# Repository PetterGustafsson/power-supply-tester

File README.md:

<p align="center">
  
</p>

# Power supply tester

**Twelve inputs. One supply. A little theatre on the desk.**

Rev D2 measurement PCB · I15 enclosure · ESP32-S3 · 240 × 240 round LCD

The tester identifies positive and return contacts from one common DC supply.
Chrome reflections, brass pins and orange locating keys give the idle display
its character. Applying voltage starts a one-second optical seating animation,
followed by live voltage, polarity and animated current artwork. The red Allied
Vision emblem at six o'clock currently recognizes the **1–2 pair**.

The opening render cycles through **idle → recognized pair → other powered pair**,
including the one-second optical seating transition. Download the
[6000 × 4500 still](output/product-render/power-supply-tester-hero.png) or
[6000 × 4500 animated master](output/product-render/power-supply-tester-three-modes-6000.gif).

*The animation uses illustrative voltage. The device uses its ADC readings to
drive the live display.*

## The current build

The October 23 firmware is the version the operator confirmed working: the
1–2 cable responds in approximately **1–2 seconds and stays powered**. Source,
the exact installed application binary, its display asset and build hashes are
included. [Build and flash guide →](docs/BUILD.md)

| Part of the project | Start here |
| --- | --- |
| Enclosure, ready to print | [I15 as-built 3MF and four STLs](case-cad/current/) |
| Preserved original CAD and earlier revisions | [CAD guide](case-cad/README.md) |
| Working measurement firmware | [Tester12VRevD source](firmware/Tester12VRevD/) |
| Exact working firmware + optical asset | [October 23 binary package](firmware/releases/d2-live-2026-10-23/) |
| PCB schematic, layout, BOM, Gerbers and CPL | [Rev D2 hardware](hardware/rev-d/README.md) |
| Finished product rendering and animation | [6K still](output/product-render/power-supply-tester-hero.png) · [6K GIF](output/product-render/power-supply-tester-three-modes-6000.gif) · [scene and regeneration guide](output/product-render/README.md) |
| Assembly poster | [A2 PDF](output/pdf/power-supply-tester-final-layout.pdf) · [full-resolution PNG](output/final-layout-poster/power-supply-tester-final-layout.png) |
| Poster scene and parts list | [Blender scene](output/final-layout-poster/final-layout.blend) · [parts manifest](output/final-layout-poster/parts-manifest.json) |
| Artwork sources and generation | [Scripts](scripts/) · [art and build guide](docs/BUILD.md#artwork-and-poster) |
| Calibration and bench testing | [Local calibration UI](tools/calibration-ui/README.txt) · [firmware/calibration guide](firmware/Tester12VRevD/README.md) |
| Timing, installation and regression evidence | [October 23 record](output/fast-response-2026-10-23/flash-evidence.json) |

## The assembly

| Hardware | Quantity | Use |
| --- | ---: | --- |
| M2 × 6 mm, black flat Phillips self-tapping screws | 6 | Four for the PCB, two for the display |
| M2.5 × 10 mm, black flat Phillips self-tapping screws | 4 | Case |
| 2 mm foam pad | 1 | USB support |
| 4-inch soft flat USB-C extension, 90° male to female | 1 | Internal USB connection |
| Twelve-core HR10A connector cable with ferrule ends | 1 | Twelve sensing inputs |
| Five-wire display harness | 1 | Display-to-PCB connection |
| Rubber feet | 4 | Base |
| Cable tie | 1 | Cable strain relief |

The [as-built print plate](case-cad/current/PSU_case_I15_as_built.3mf) contains
the base, shell, crown and display retainer. The preserved original I15 package
also contains the earlier printed shim; the current assembly uses the foam pad.
The poster shows the display as unpowered black glass and the USB cable straight.

Selected components: [screw assortment](https://www.amazon.com/dp/B0G24Z3P66),
[USB extension](https://www.amazon.com/dp/B0D9XGFW3W).

## Display art

- **Idle:** numbered brass contacts and orange orientation sheen.
- **Seating:** optical travel across one second.
- **Recognized pair:** static red emblem, cold-to-gold discharge and a spectral helix.
- **Other pairs:** muted crossed emblem with live polarity effects.

The previews show the visual design. The firmware samples 21 travel frames
across the one-second transition; playback and render timing are recorded in
the device logs. The electrical overlays illustrate classified polarity.

## Electronics and validation

The non-touch Waveshare ESP32-S3-LCD-1.28 handles the display and measurement
firmware. Four ADS1115 devices on the isolated measurement PCB provide twelve
sensing channels and a reference channel. See the
[hardware guide](hardware/rev-d/README.md) for the supported connection model,
limits, pin numbering and harness wiring.

The current prototype uses the measured input-1 gain shared with inputs 2–12,
with copied calibration provenance retained. Complete individual-channel
calibration and independent accuracy qualification remain in the
[calibration guide](firmware/Tester12VRevD/README.md). Noisy batches can produce
a filtered provisional LCD estimate while the strict measurement CSV rejects
them. The display response improvement preserves that distinction.

## Build and test

```sh
python3 -m venv .venv
source .venv/bin/activate
python -m pip install -r requirements.txt

clang++ -std=c++17 -O2 hardware/rev-d/scripts/test_preview_detection.cpp -o /tmp/tester-preview
/tmp/tester-preview
python hardware/rev-d/scripts/test_integration.py
python hardware/rev-d/scripts/test_calibration_commands.py
```

These tests use simulated hardware and do not open the tester's USB port.
Firmware compilation, binary recovery, artwork generation and poster rendering
are documented in [BUILD.md](docs/BUILD.md).

## Project map

```text
case-cad/        Current printable enclosure and historical CAD/reference exports
firmware/        Measurement source, display demos and the working binary package
hardware/        KiCad sources, manufacturing exports, sourcing and validation
scripts/         Artwork, optical assets, enclosure export and poster generation
tools/           Local calibration and supply-test interface
assets/          Fonts and their license/source records
docs/            Build guide and README artwork
output/          Posters, display assets and engineering/test evidence
references/      Manufacturer drawings and reference material
```

Historical hardware packages and art studies are retained with their revision
names. The links in **The current build** identify this prototype's baseline.
Third-party fonts, code, logos and models retain their original terms; see
[third-party notices](THIRD_PARTY_NOTICES.md).

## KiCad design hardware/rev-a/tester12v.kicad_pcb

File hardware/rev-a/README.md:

# 12 V pin-voltage tester — Rev A prototype

This is an actual KiCad 9 schematic and routed PCB, designed for a nominal **12 V DC source on any two of twelve inputs**, in either polarity. The other inputs are normally open. It measures voltage; it does not supply 12 V, switch power between connector pins, perform a load test, or prove which wire is earth/chassis ground.

**Status: prototype fabrication package with completed computer checks. No assembled Rev A board has been bench tested.** Component substitutions, assembled-board accuracy, power sequencing, and the display harness still require the first-article checks below. Do not interpret the simulations as a guarantee of operation.

The copper, holes, placements, and board outline in this render come from `tester12v.kicad_pcb`. Standard library component bodies are representative; the RECOM converter uses a generic SOIC body with a similar outline. This is not the earlier generated concept image. The **Waveshare ESP32-S3-LCD-1.28 non-touch** round display/controller connects by a five-wire harness and mounts separately. Display mounting holes or an enclosure are not part of this PCB.

## Files to use

- `../tester12v-rev-a-jlc-order.zip`: concise order handoff. Extract it, then upload `PCB-Gerbers.zip`, `BOM.csv` and `CPL.csv` to their respective JLC steps. Read `ORDER-INSTRUCTIONS.txt` first; U7 sourcing remains unresolved. This bundle contains the primary optimized BOM only.
- `tester12v.kicad_pro`, `tester12v.kicad_sch`, `bank1..3.kicad_sch`, `tester12v.kicad_pcb`: editable native design.
- `previews/schematic.pdf`, `previews/assembly.pdf`: circuit and component-location drawings.
- `previews/tester12v.step`: board/component geometry for mechanical review, subject to the model limitation above.
- `manufacturing/tester12v-rev-a-fabrication.zip`: Gerber and drill package for bare PCBs.
- `manufacturing/bom-grouped.csv`, `manufacturing/placements-smd.csv`: component purchasing/assembly information. R43 and R44 are **DNP**. J1–J4 are through-hole parts, omitted from the SMD placement file.
- `manufacturing/jlc-bom.csv`, `manufacturing/jlc-cpl.csv`: JLC upload files with exact library codes and all 114 fitted components, including J1–J4. See the sourcing blocker below before releasing an order.
- `sourcing/JLC-BOM-review.xlsx`, `sourcing/jlc-review.json`: dated price, stock, substitution and fee comparison.
- `validation/REPORT.md`: methods, results, assumptions, and limits of the checks.
- `../../firmware/Tester12V/`: live measurement firmware. The older `ConnectorDisplay` sketch is still the simulated animation demo.

## JLC sourcing update — 2026-09-30

The BOM now uses 24 exact JLC part numbers: eight Basic and sixteen Extended. Twenty-three part types had sufficient displayed stock for the nominal two-board quantity. **U7, RECOM R05C05TE05S-R / C5338283, had zero stock and requires preorder; no lead time was displayed.** Obtain its confirmed delivery and price before releasing the assembly order. This update does not make the whole assembly immediately available.

Four ordinary resistor types and four capacitor types now use Basic parts. This avoids eight Economic PCBA loading fees, approximately **$24.56 per order** at JLC's published $3.07 rate. It is a fee saving, not a claim that the entire order is $24.56 cheaper: the stocked switch packaging costs more than its preorder-only alternative. Standard PCBA charges loading for Basic parts too, so the same saving does not apply there. [JLC assembly fee schedule](https://jlcpcb.com/help/article/pcb-assembly-price).

The 165 kΩ, 10 kΩ and 100 kΩ precision resistors remain the original Yageo 0.1%, 25 ppm/K parts. C1–C12/C28 change from an unavailable Murata part (preorder minimum 799) to stocked Yageo C62774, preserving 1 nF, 5%, 50 V and C0G/NP0. All other capacitor substitutions preserve nominal capacitance, tolerance and dielectric, with equal or higher voltage ratings. C24's Samsung C45783 is NRND but had over four million pieces in JLC stock; it is selected for this small prototype order, with a fresh lifecycle review required for ongoing production. MLCC effective capacitance and startup/shutdown behavior still require bench verification.

U4–U6 use stocked **ADG4612BRUZ-REEL7 / C207399**, the same TSSOP-16 chip with different shipping packaging. JLC displayed 41 pieces and $6.7450 each. The optional `manufacturing/jlc-bom-preorder-switches.csv` selects the original **ADG4612BRUZ / C657391** instead: zero stock, estimated nine-day lead time, MOQ four and estimated $2.7916 each. Six fitted switches could cost about $23.72 less, before attrition; consider this only if its confirmed lead time fits the converter wait. Use one BOM, not both.

At displayed 1+ unit prices, the primary BOM's nominal fitted parts for two boards total **$93.16**, including a **$20.97 unconfirmed converter preorder estimate**. The Economic loading allowance is another $49.12. These are not a checkout quote: PCB fabrication, setup, placement, attrition/spares, minimum-order overhead, shipping, tax, LCD module and harness are excluded. Nothing is reserved or ordered.

The JLC CPL uses the same origin as the Gerbers: X right, Y upward, millimetres; negative Y is intentional. J1–J4 use the centre of the footprint's F.Fab body rather than the pin-1 origin. SMD positions and rotations are unchanged. Inspect JLC's placement preview against `previews/assembly.pdf`, especially polarized parts and connector orientation; JLC library rotation conventions have not been validated in an order. Resolve converter sourcing, part matching and manufacturer DFM before payment. The populated count is 114; R43/R44 and test pads are excluded.

Sourcing changed only MPN/manufacturer/library metadata. The native PCB now also contains the optimized purchasing fields. All circuit values, pin nets, footprint geometry and routing are unchanged. Gerbers, drills, DNP-filtered stencil, placements, schematic and assembly PDFs have been regenerated. Exact drawing commands match the prior release after excluding export timestamps. ERC/DRC and the 356-pad connectivity audit pass; DC/transient and host firmware tests passed for the same unchanged circuit. No assembled-board tests have been performed.

## Board and electrical specification

| Item | Rev A |
|---|---|
| Board | 90 × 80 mm; two copper layers; 1.6 mm FR-4; 1 oz copper |
| Minimum routed trace / clearance | 0.20 mm / 0.20 mm netclass clearance |
| Through vias | 0.60 mm diameter / 0.30 mm finished drill |
| Mounting | Four 2.7 mm non-plated holes; centers (3,3), (87,3), (3,77), (87,77) mm |
| Inputs | Twelve high-impedance sense terminals; three four-position 3.5 mm screw terminals |
| Normal input range | 0–18 V DC between the active pair; optimized for 12 V |
| Fault target | 48 V DC differential miswire survival target, **not a qualified rating or accurate measurement range** |
| Power | Separate USB-domain 5 V and 3.3 V through J4 |
| Isolation | Isolated DC/DC plus I²C isolator; no copper crosses the 2.7 mm isolation corridor |
| ADCs | Three ADS1115, addresses 0x48, 0x49, 0x4A; ±4.096 V ADC scale; 3.3 V supply |
| Display | Existing Waveshare ESP32-S3-LCD-1.28, 240 × 240 GC9A01 |
| Accuracy | ±0.15 V around 12 V after calibration is a **bench acceptance target**, not a measured specification |
| Environment | Initial qualification at room temperature, clean/dry PCB, low-energy DC supplies |

The isolated ground floats with the connected supply. A displayed negative terminal is the lower-voltage terminal of the detected pair, not an earth-ground identification. Multiple rails and multiple connected returns can be ambiguous; the firmware rejects patterns that do not fit one live pair. This board is not a mains, CAT-rated, or automotive transient instrument. It is not a continuity tester for unpowered wires.

## Circuit operation

Each input passes through two 165 kΩ resistors. A 12 V Zener limits the source-side voltage of an ADG4612 switch; a 100 kΩ source bleed defines its voltage during startup. The switch connects to a 10 kΩ bias resistor, a 1 nF filter, and one ADC input. All three precision resistor values use 0.1% parts. The 100 kΩ bleed prevents the protection switch from staying in overvoltage isolation when a 12 V source is attached before USB power.

An OPA320 buffers half the isolated 3.3 V rail. R39 is a 220 Ω bleed that also discharges the bias node when power is removed. The TLV809EA30 supervisor enables the switches after the analog supply is established and disables them as the rail falls. D13 provides the TLV75533 regulator's output-to-input reverse-current path. Do not substitute the earlier MCP6001/1 kΩ/100 nF trial values.

The nominal differential scale, neglecting switch resistance and ADC loading, is:

`Vpair = (1 + 330k/10k + 330k/100k) × (VADC+ − VADC−) = 37.3 × ΔVADC`

An open ADC channel is approximately 1.50 V. At 12 V, the selected pair is approximately 1.34 V and 1.66 V. Firmware uses all twelve measurements to find the pair and its polarity. ADC loading, component tolerance, leakage, and different ADC gain errors require calibration for accurate readings. Scans are sequential, not a simultaneous oscilloscope capture.

## Display harness and power

Use the PCB connector's **pin numbers**, confirmed against the assembly drawing; do not infer wire order from a photograph. J4 is a JST XH five-position header. The mating housing is XHP-5 with appropriate XH contacts and insulated wire.

| J4 pin | PCB net | Existing Waveshare header connection |
|---|---|---|
| 1 | USB5V | Regulated USB-domain 5 V; H2 pin 3 VSYS is conditional as described below |
| 2 | USB_GND | H2 pin 1 GND |
| 3 | HOST3V3 | H2 pin 4, 3V3 |
| 4 | SDA_HOST | H2 pin 5, GPIO6 |
| 5 | SCL_HOST | H2 pin 7, GPIO7 |

The Waveshare schematic puts a Schottky diode between USB VBUS and VSYS. **Verify at least 4.5 V at U7's input after F1 while running**, and no more than 5.5 V. VSYS from a weak cable or low USB supply may not meet that minimum. If needed, feed J4 pin 1 from a regulated 5 V USB breakout/supply, sharing only the USB-domain ground. Do not connect an external 5 V source to the display's VSYS while also driving it from USB without reviewing that supply arrangement. Battery-only display operation does not provide the required tester supply.

R43/R44 stay unpopulated because the Waveshare module already has 4.7 kΩ I²C pull-ups on GPIO6/7. The isolated side has its own pull-ups. Use a short harness, initially no more than about 15 cm, and 100 kHz I²C. Never connect a DUT wire to J4 or bridge AGND to USB_GND during normal operation.

## First-article bench procedure

1. Inspect IC orientation, all diode cathodes, resistor values, solder bridges, and the 12 input paths against the assembly PDF. Confirm R43/R44 are absent. Clean flux before measuring leakage or calibrating.
2. With no DUT connected, check for supply shorts and for an unintended DC connection between USB_GND and AGND. Use an ordinary continuity/resistance test; do not apply a high-voltage insulation tester to the assembled board.
3. Power through J4 from a current-limited 5 V supply, initially limiting the tester's 5 V feed to 100 mA. Supply HOST3V3 from the display/controller. Check U7 input ≥4.5 V, isolated output near 5 V, A3V3 near 3.3 V, VBIAS near 1.65 V, and EN near 3.3 V after the supervisor delay. Investigate a sustained tester 5 V current above 100 mA. Measure actual consumption; the current budget is not a bench result.
4. Load the `Tester12V` sketch using the existing project flashing method. Its serial console runs at 115200 baud. Check all three ADC addresses and all twelve ADC readings near 1.50 V. Confirm unplugging the measurement board produces `ADC FAULT`, not a retained voltage.
5. Use an **isolated, current-limited** 12 V source, initially limited to 10 mA, between terminals 1 and 2. Check both polarities. The device draws only tens of microamps from this source; it does not load-test it.
6. Run all 132 ordered positive/negative pin pairs using `validation/bench-pairs.csv`. Record displayed pair, polarity, voltage, and the reference DMM reading. Calibrate before evaluating the ±0.15 V target. Also test no source, shorted pair, and an intentionally ambiguous multi-wire connection.
7. Check 3.3, 5, 9, 12, 15, and 18 V with representative pairs within one ADC and across different ADCs. Check settled accuracy, rise/fall response, and noise over at least 60 seconds.
8. Repeat power cycles with the 12 V DUT attached first, USB attached first, and removal/reconnection of each. Observe A3V3, VBIAS, EN, and representative ADC nodes with an isolated/differential probe. A grounded oscilloscope lead must not inadvertently bridge the isolation boundary. Check ADC nodes stay between AGND −0.3 V and A3V3 +0.3 V, and verify no persistent back-powering.
9. Only after the normal tests pass, evaluate the 24/48 V DC miswire target with a current-limited source, monitoring internal nodes and supply current. Do not claim a 48 V rating from the computer model alone. ESD, EMC, thermal extremes, and fast transients require separate qualification.

Record measured results and any board changes before ordering a larger batch.

## Calibration

Calibrate every channel with two known input voltages referred to **AGND on the isolated side**, using a floating precision source and DMM. This is a bench calibration arrangement, not the normal floating-pair connection. Do not connect the calibrator's return to USB_GND.

For each input, record the raw ADC voltage from serial CSV at a measured 0 V and a measured approximately +12 V on that terminal. Keep all other input terminals open. Average at least 32 settled readings per point. Calculate:

`gain = (Vhigh − Vlow) / (ADChigh − ADClow)`

`offset = Vlow − gain × ADClow`

Send `cal <pin 1..12> <gain> <offset>` over the serial console. Values persist in the ESP32's nonvolatile storage. For example, a measured gain near 37.3 is expected; the offset is often a large negative value because of the internal bias. **Use measured values, not this nominal example.** Complete all twelve channels; the firmware shows `FINISH CAL` while calibration is partial. `defaults` clears calibration and restores the nominal uncalibrated scale. Then disconnect the AGND calibration return and repeat floating-pair tests, including reversed polarity and cross-ADC pairs.

## Design sources

Pin assignments, ratings, and footprints were checked against the manufacturers' documents: [ADS1115](https://www.ti.com/lit/ds/symlink/ads1115.pdf), [ADG4612](https://www.analog.com/media/en/technical-documentation/data-sheets/adg4612_4613.pdf), [ISO1640B](https://www.ti.com/lit/ds/symlink/iso1640.pdf), [RECOM converter](https://recom-power.com/pdf/Econoline/RxxC05TExxS.pdf), [TLV755P](https://www.ti.com/lit/ds/symlink/tlv755p.pdf), [TLV809E family](https://www.ti.com/lit/ds/symlink/tlv803e.pdf), [OPA320](https://www.ti.com/lit/ds/symlink/opa320.pdf), [BZT52H](https://assets.nexperia.com/documents/data-sheet/BZT52H_SER.pdf), [PMEG2010ER](https://assets.nexperia.com/documents/data-sheet/PMEG2010ER.pdf), [Phoenix 1984633 terminal](https://www.phoenixcontact.com/en-us/products/printed-circuit-board-terminal-pt-15-4-35-h-1984633), and [Waveshare documentation](https://docs.waveshare.com/ESP32-S3-LCD-1.28).

Available PDF snapshots and source URLs are in `sources/`. Some manufacturer downloads were blocked; their documents were reviewed through the browser instead. Parts have not been reserved and stock, price, fabrication lead time, and assembler substitutions have not been confirmed.

The native PCB is the authoritative finished copper layout. `scripts/build_kicad.py` recreates **unrouted placement** and overwrites the PCB; run it only in a separate working copy. The routing scripts record the construction steps and are not a one-command regeneration of the finished release.

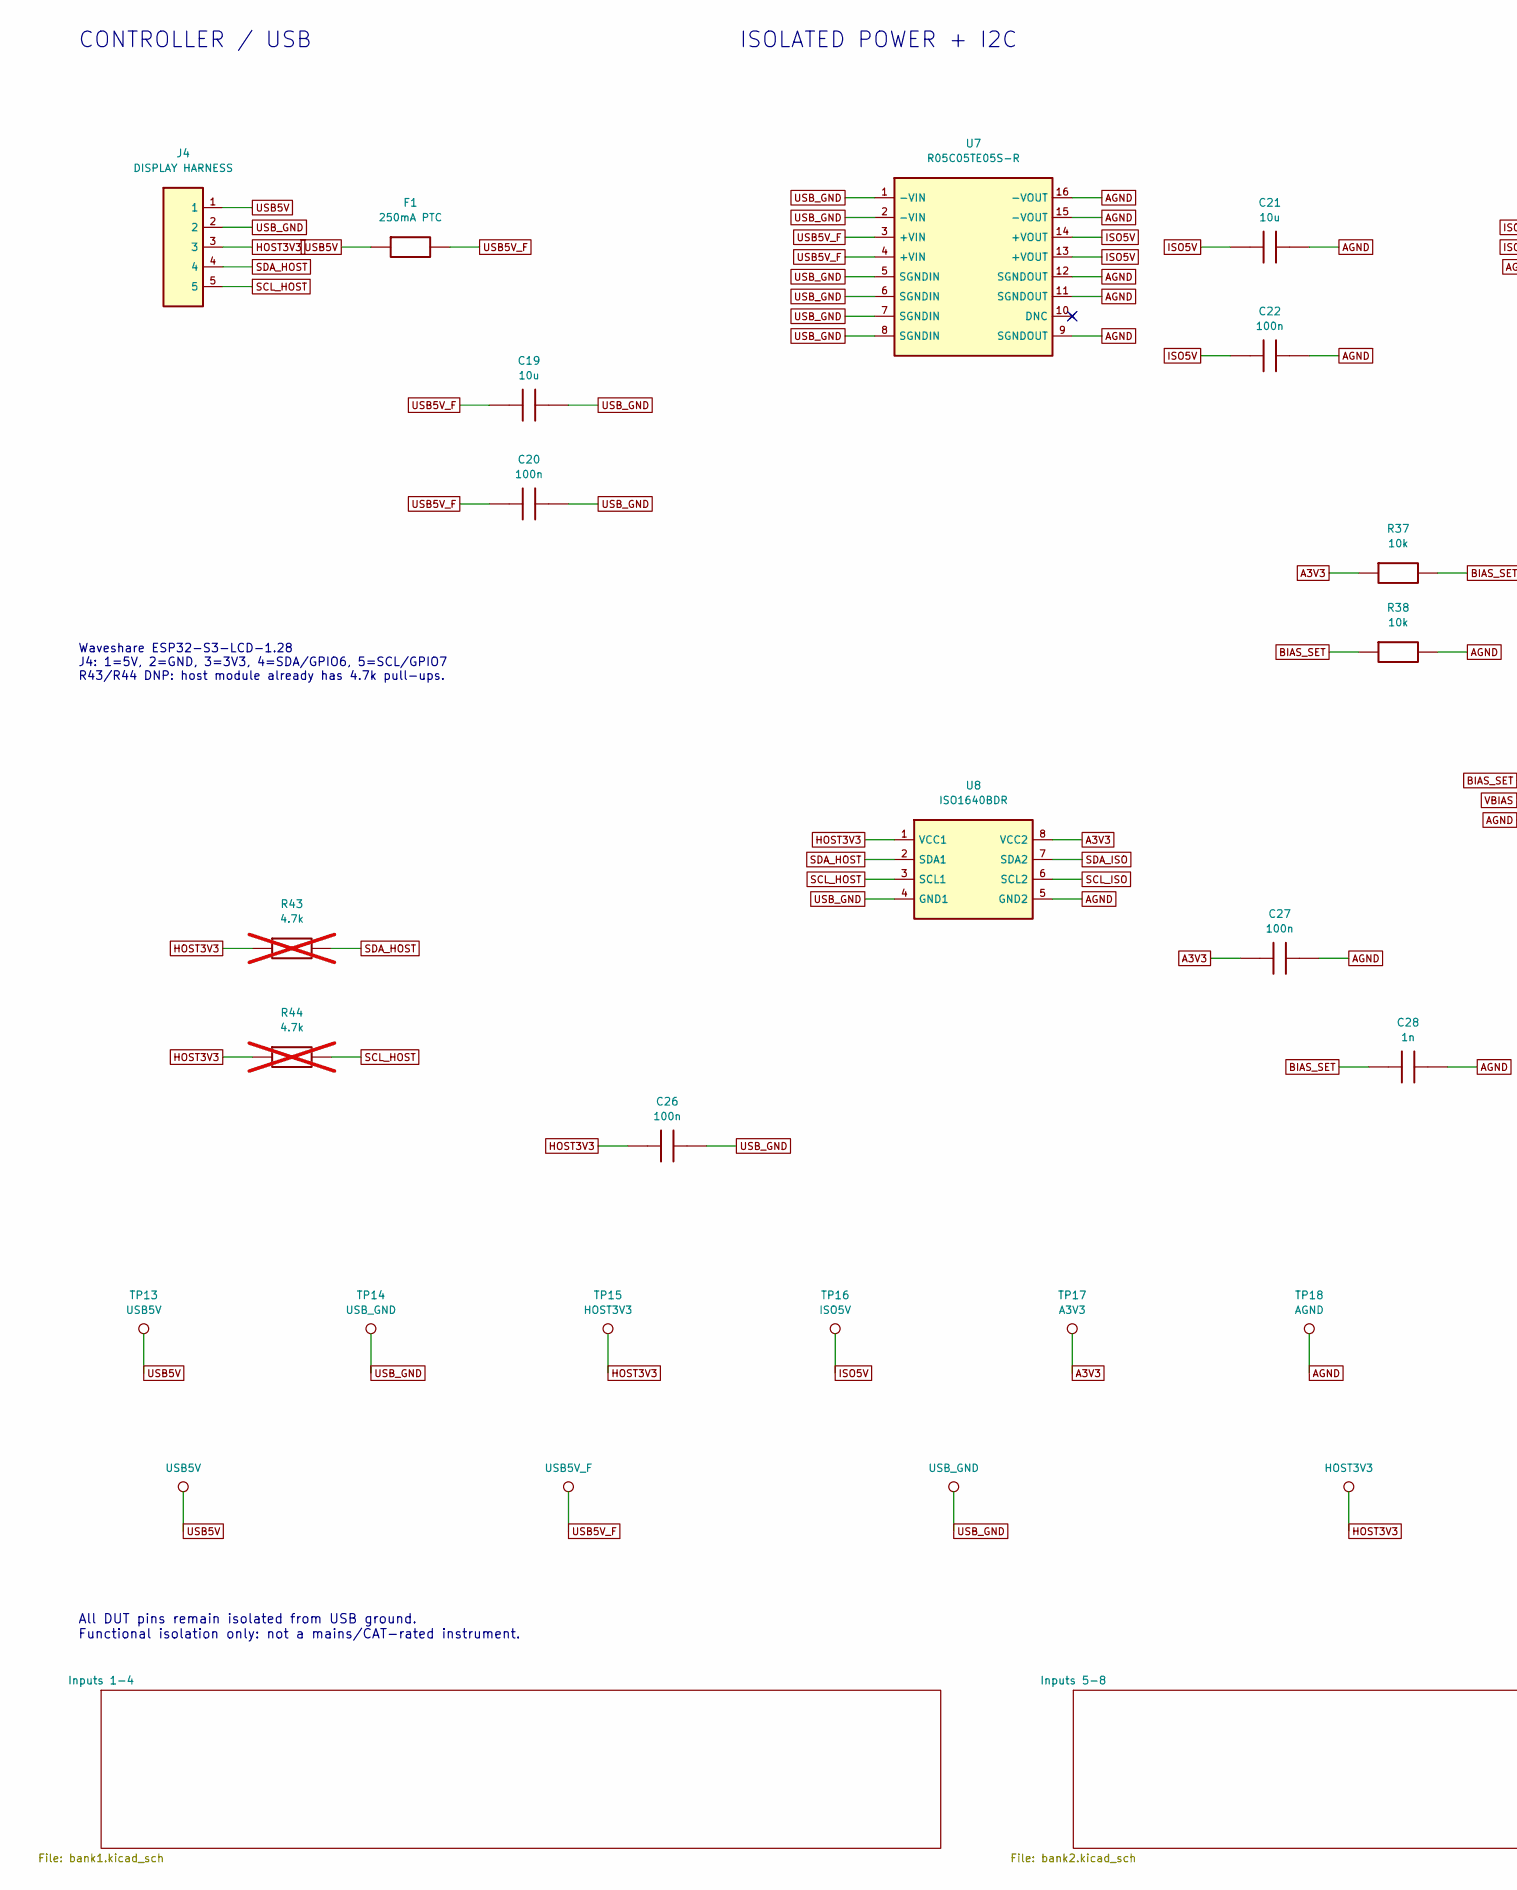
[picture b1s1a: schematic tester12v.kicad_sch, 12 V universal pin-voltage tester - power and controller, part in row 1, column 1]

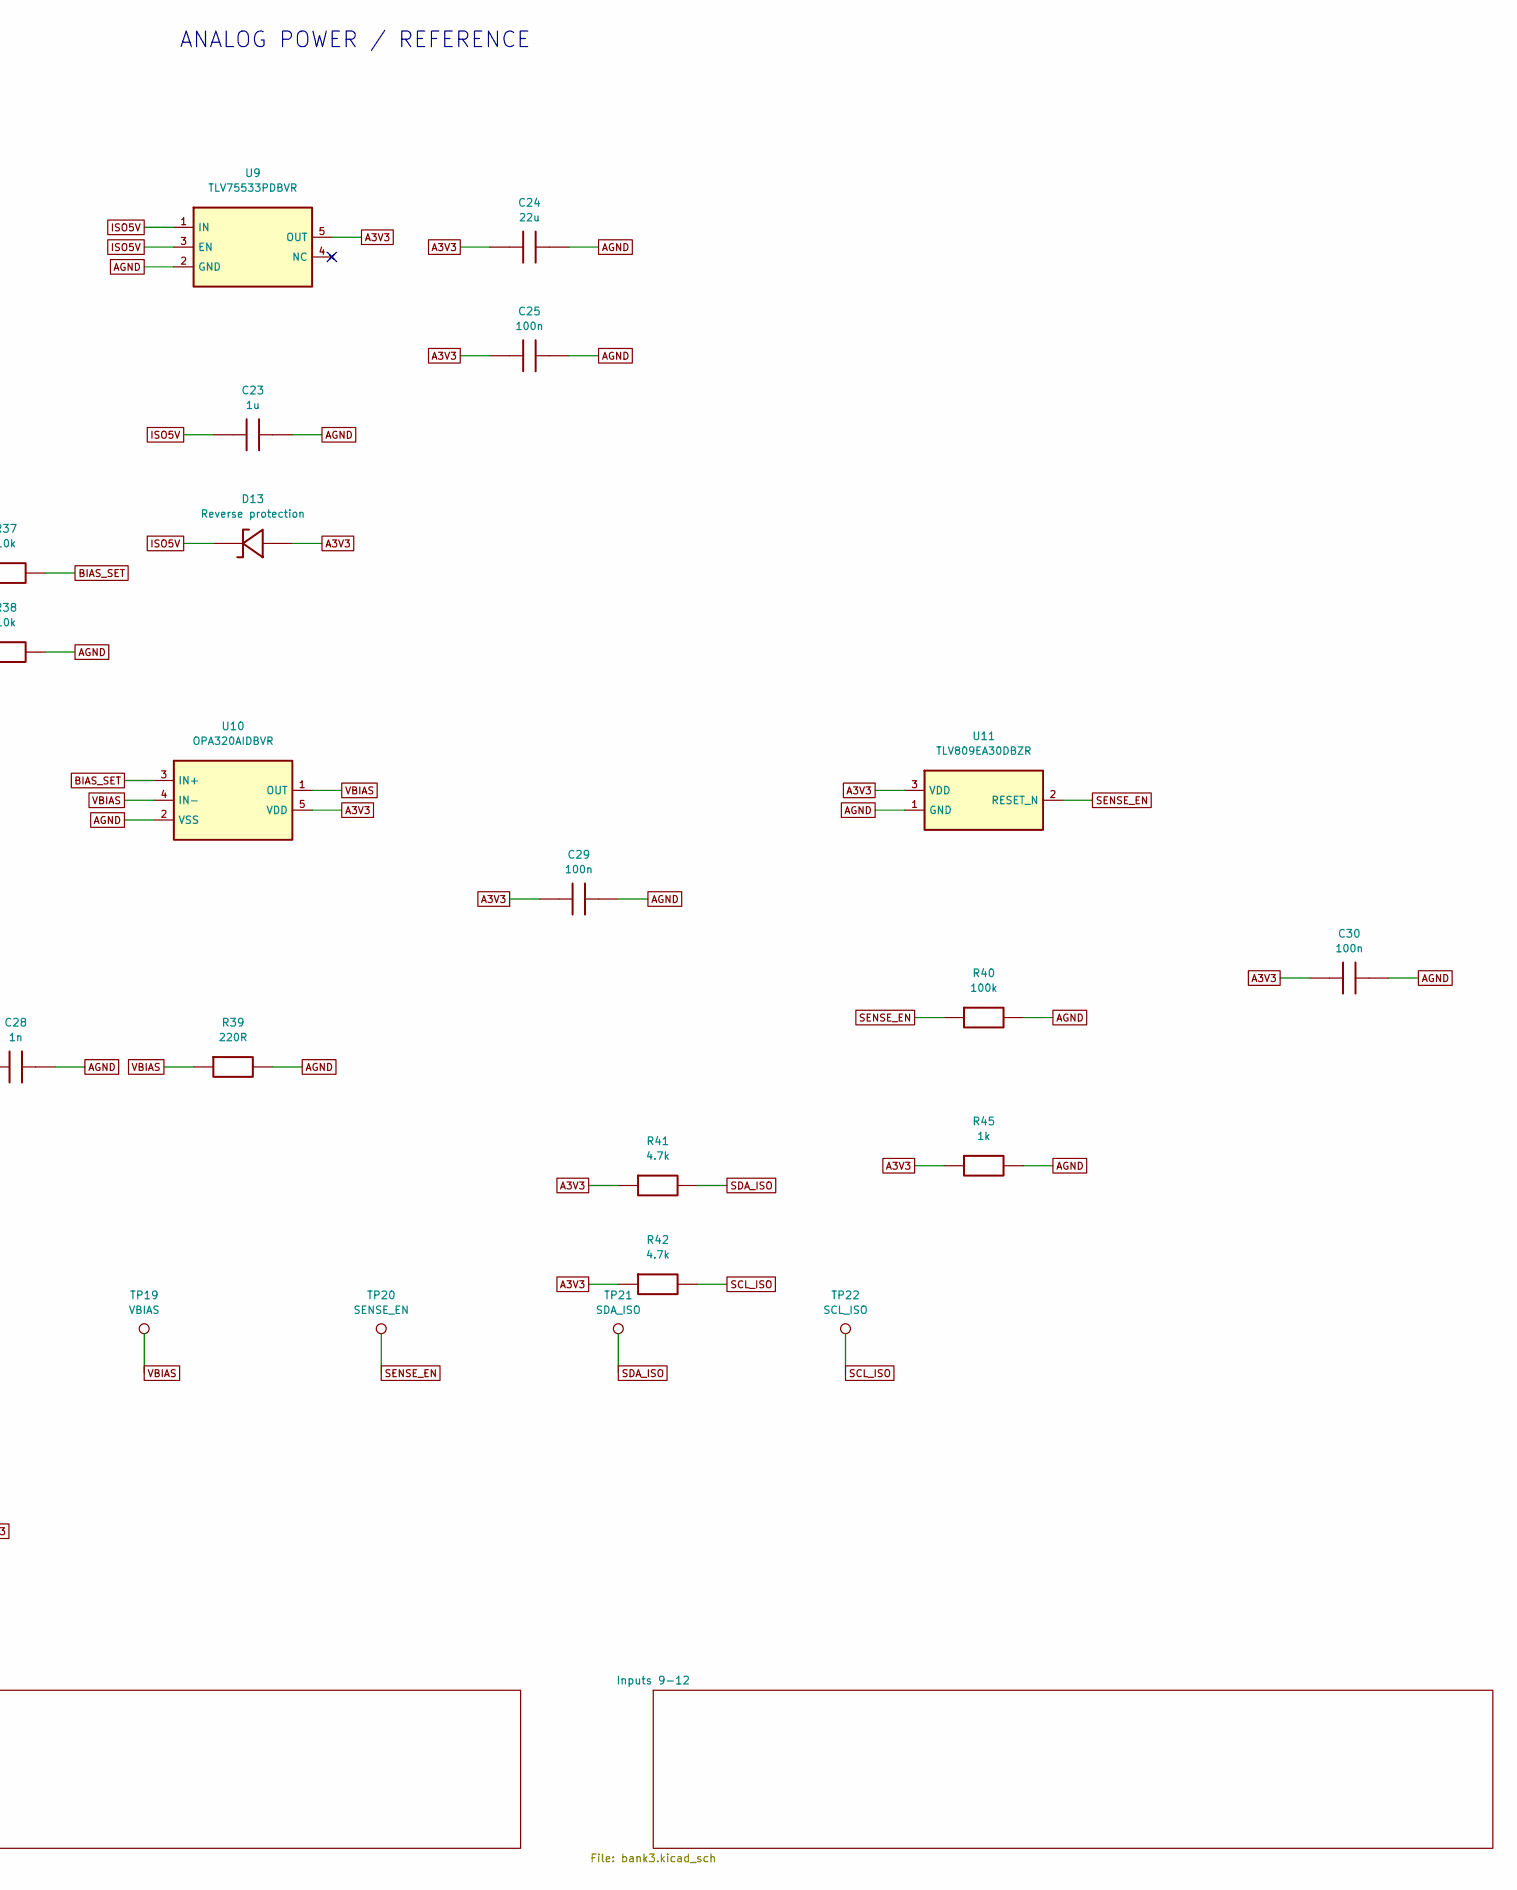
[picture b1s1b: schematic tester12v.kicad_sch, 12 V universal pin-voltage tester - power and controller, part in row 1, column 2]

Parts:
C19, C21: 10u; C_0805_2012Metric; MPN CL21A106KAYNNNE; LCSC C15850
C20, C22, C25, C26, C27, C29, C30: 100n; C_0805_2012Metric; MPN CC0805KRX7R9BB104; LCSC C49678
C23: 1u; C_0805_2012Metric; MPN CL21B105KBFNNNE; LCSC C28323
C24: 22u; C_0805_2012Metric; MPN CL21A226MAQNNNE; LCSC C45783
C28: 1n; C_0805_2012Metric; MPN CC0805JRNPO9BN102; LCSC C62774
D13: Reverse protection; Nexperia_CFP3_SOD-123W; MPN PMEG2010ER,115; LCSC C82288
F1: 250mA PTC; Fuse_1206_3216Metric; MPN 1206L025/24YR; LCSC C3762322
J4: DISPLAY HARNESS; JST_XH_B5B-XH-A_1x05_P2.50mm_Vertical; MPN B5B-XH-A(LF)(SN); LCSC C157991
R37, R38: 10k; R_0805_2012Metric; MPN RT0805BRD0710KL; LCSC C110775
R39: 220R; R_0805_2012Metric; MPN 0805W8F2200T5E; LCSC C17557
R40: 100k; R_0805_2012Metric; MPN 0805W8F1003T5E; LCSC C149504
R41, R42: 4.7k; R_0805_2012Metric; MPN 0805W8F4701T5E; LCSC C17673
R43, R44: 4.7k; R_0805_2012Metric; MPN 0805W8F4701T5E; LCSC C17673; not fitted
R45: 1k; R_0805_2012Metric; MPN 0805W8F1001T5E; LCSC C17513
TP13: USB5V; TestPoint_Pad_D1.5mm
TP14: USB_GND; TestPoint_Pad_D1.5mm
TP15: HOST3V3; TestPoint_Pad_D1.5mm
TP16: ISO5V; TestPoint_Pad_D1.5mm
TP17: A3V3; TestPoint_Pad_D1.5mm
TP18: AGND; TestPoint_Pad_D1.5mm
TP19: VBIAS; TestPoint_Pad_D1.5mm
TP20: SENSE_EN; TestPoint_Pad_D1.5mm
TP21: SDA_ISO; TestPoint_Pad_D1.5mm
TP22: SCL_ISO; TestPoint_Pad_D1.5mm
U7: R05C05TE05S-R; R05C05TE05S; MPN R05C05TE05S-R; LCSC C5338283
U8: ISO1640BDR; SOIC-8_3.9x4.9mm_P1.27mm; MPN ISO1640BDR; LCSC C5122339
U9: TLV75533PDBVR; SOT-23-5; MPN TLV75533PDBVR; LCSC C404027
U10: OPA320AIDBVR; SOT-23-5; MPN OPA320AIDBVR; LCSC C92494
U11: TLV809EA30DBZR; SOT-23; MPN TLV809EA30DBZR; LCSC C2860914

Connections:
A3V3: C24.1, C25.1, C27.1, C29.1, C30.1, D13.2, R37.1, R41.1, R42.1, R45.1, TP17.1, U8.8 (VCC2), U9.5 (OUT), U10.5 (VDD), U11.3 (VDD); also elsewhere on the board
AGND: C21.2, C22.2, C23.2, C24.2, C25.2, C27.2, C28.2, C29.2, C30.2, R38.2, R39.2, R40.2, R45.2, TP18.1, U7.9 (SGNDOUT), U7.11 (SGNDOUT), U7.12 (SGNDOUT), U7.15 (-VOUT), U7.16 (-VOUT), U8.5 (GND2), U9.2 (GND), U10.2 (VSS), U11.1 (GND); also elsewhere on the board
BIAS_SET: C28.1, R37.2, R38.1, U10.3 (IN+)
HOST3V3: C26.1, J4.3, R43.1, R44.1, TP15.1, U8.1 (VCC1)
ISO5V: C21.1, C22.1, C23.1, D13.1, TP16.1, U7.13 (+VOUT), U7.14 (+VOUT), U9.1 (IN), U9.3 (EN); also elsewhere on the board
SCL_HOST: J4.5, R44.2, U8.3 (SCL1)
SCL_ISO: R42.2, TP22.1, U8.6 (SCL2); also elsewhere on the board
SDA_HOST: J4.4, R43.2, U8.2 (SDA1)
SDA_ISO: R41.2, TP21.1, U8.7 (SDA2); also elsewhere on the board
SENSE_EN: R40.1, TP20.1, U11.2 (RESET_N); also elsewhere on the board
USB5V: F1.1, J4.1, TP13.1
USB5V_F: C19.1, C20.1, F1.2, U7.3 (+VIN), U7.4 (+VIN)
USB_GND: C19.2, C20.2, C26.2, J4.2, TP14.1, U7.1 (-VIN), U7.2 (-VIN), U7.5 (SGNDIN), U7.6 (SGNDIN), U7.7 (SGNDIN), U7.8 (SGNDIN), U8.4 (GND1)
VBIAS: R39.1, TP19.1, U10.1 (OUT), U10.4 (IN-); also elsewhere on the board

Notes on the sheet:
CONTROLLER / USB
ISOLATED POWER + I2C
ANALOG POWER / REFERENCE
Waveshare ESP32-S3-LCD-1.28 J4: 1=5V, 2=GND, 3=3V3, 4=SDA/GPIO6, 5=SCL/GPIO7 R43/R44 DNP: host module already has 4.7k pull-ups.
All DUT pins remain isolated from USB ground. Functional isolation only: not a mains/CAT-rated instrument.

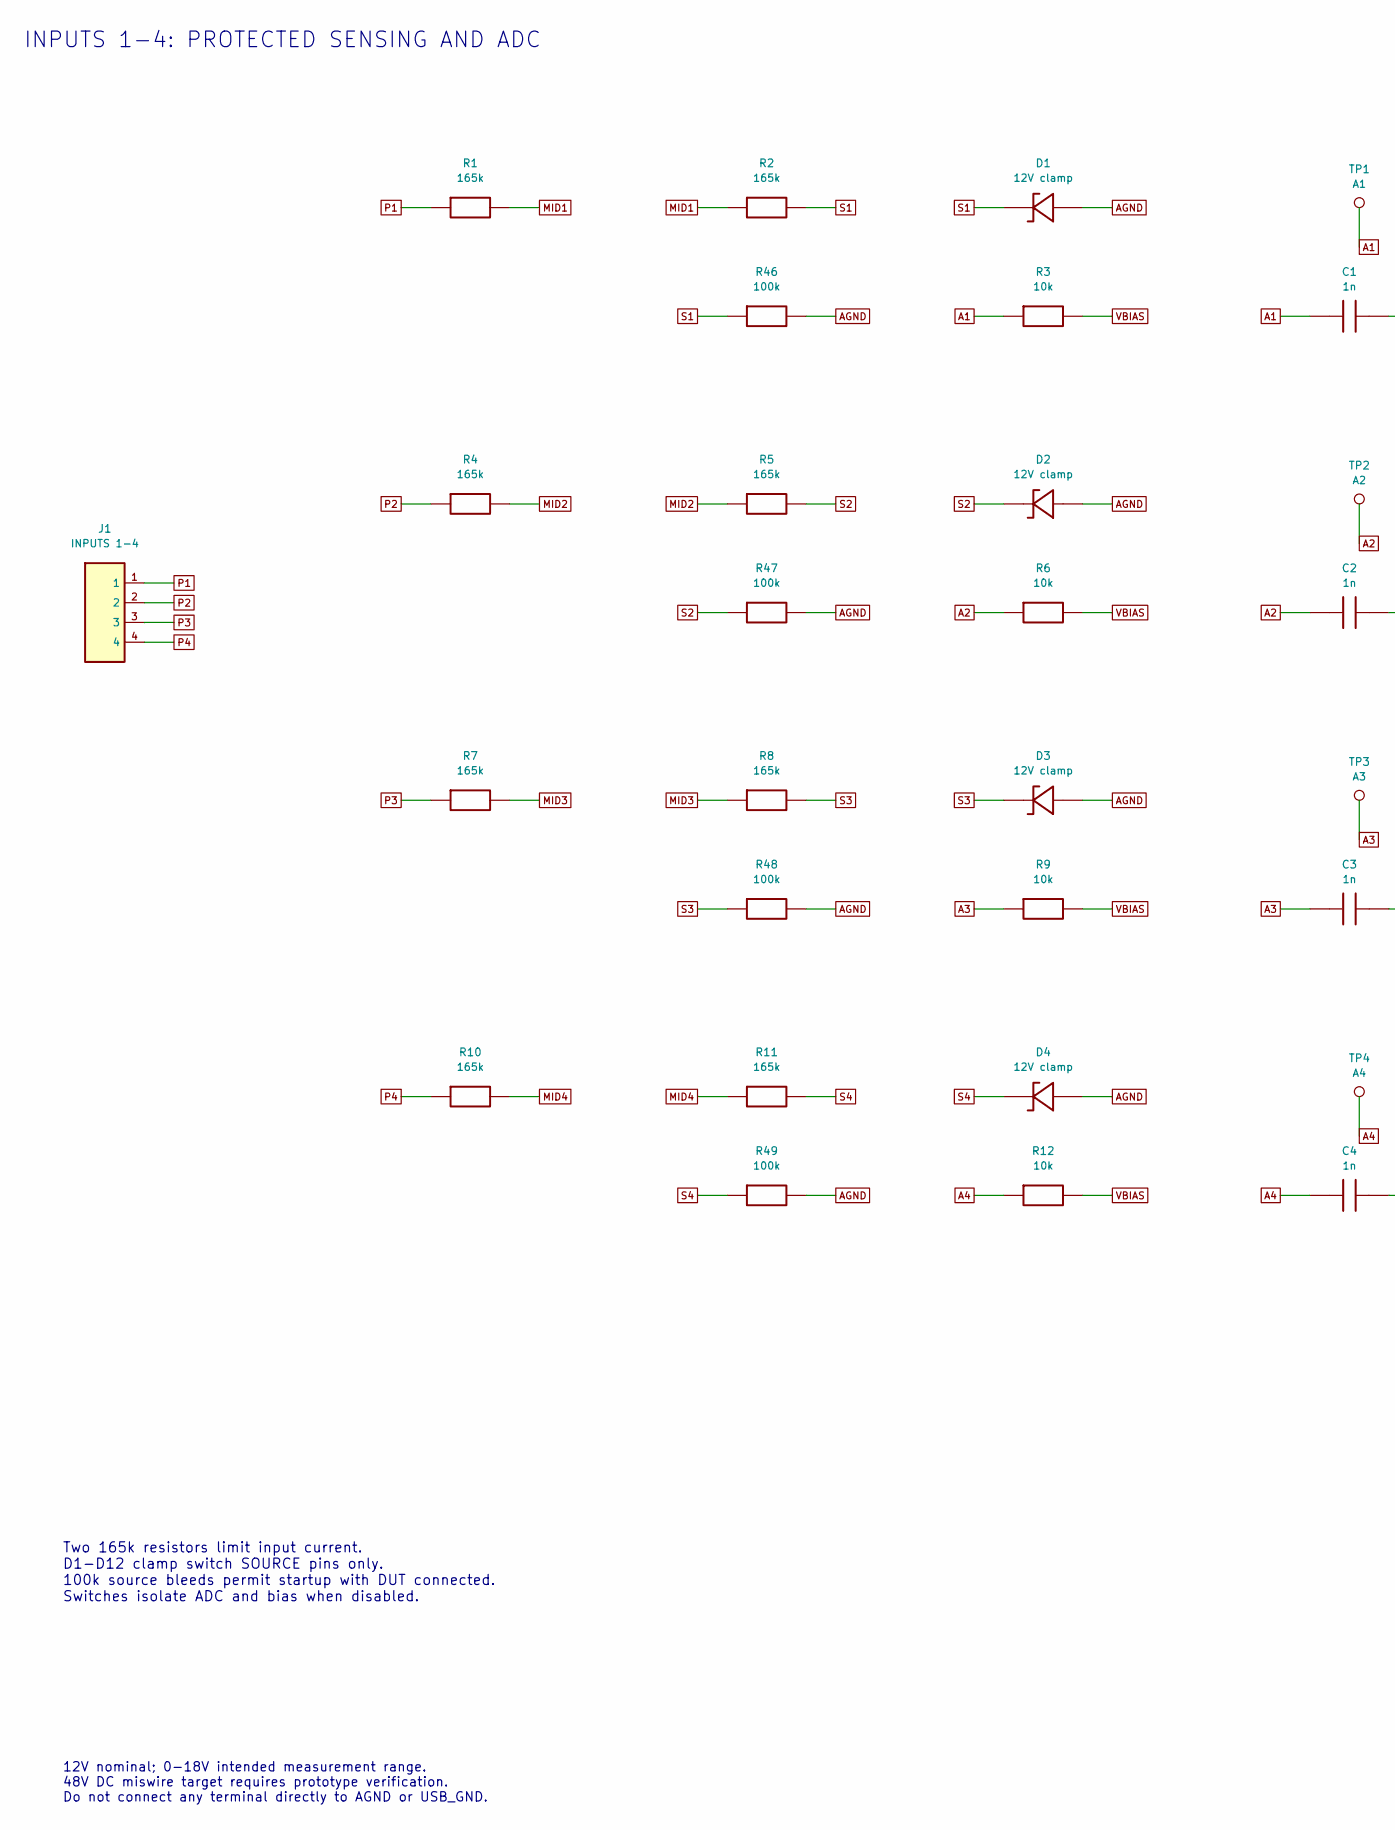
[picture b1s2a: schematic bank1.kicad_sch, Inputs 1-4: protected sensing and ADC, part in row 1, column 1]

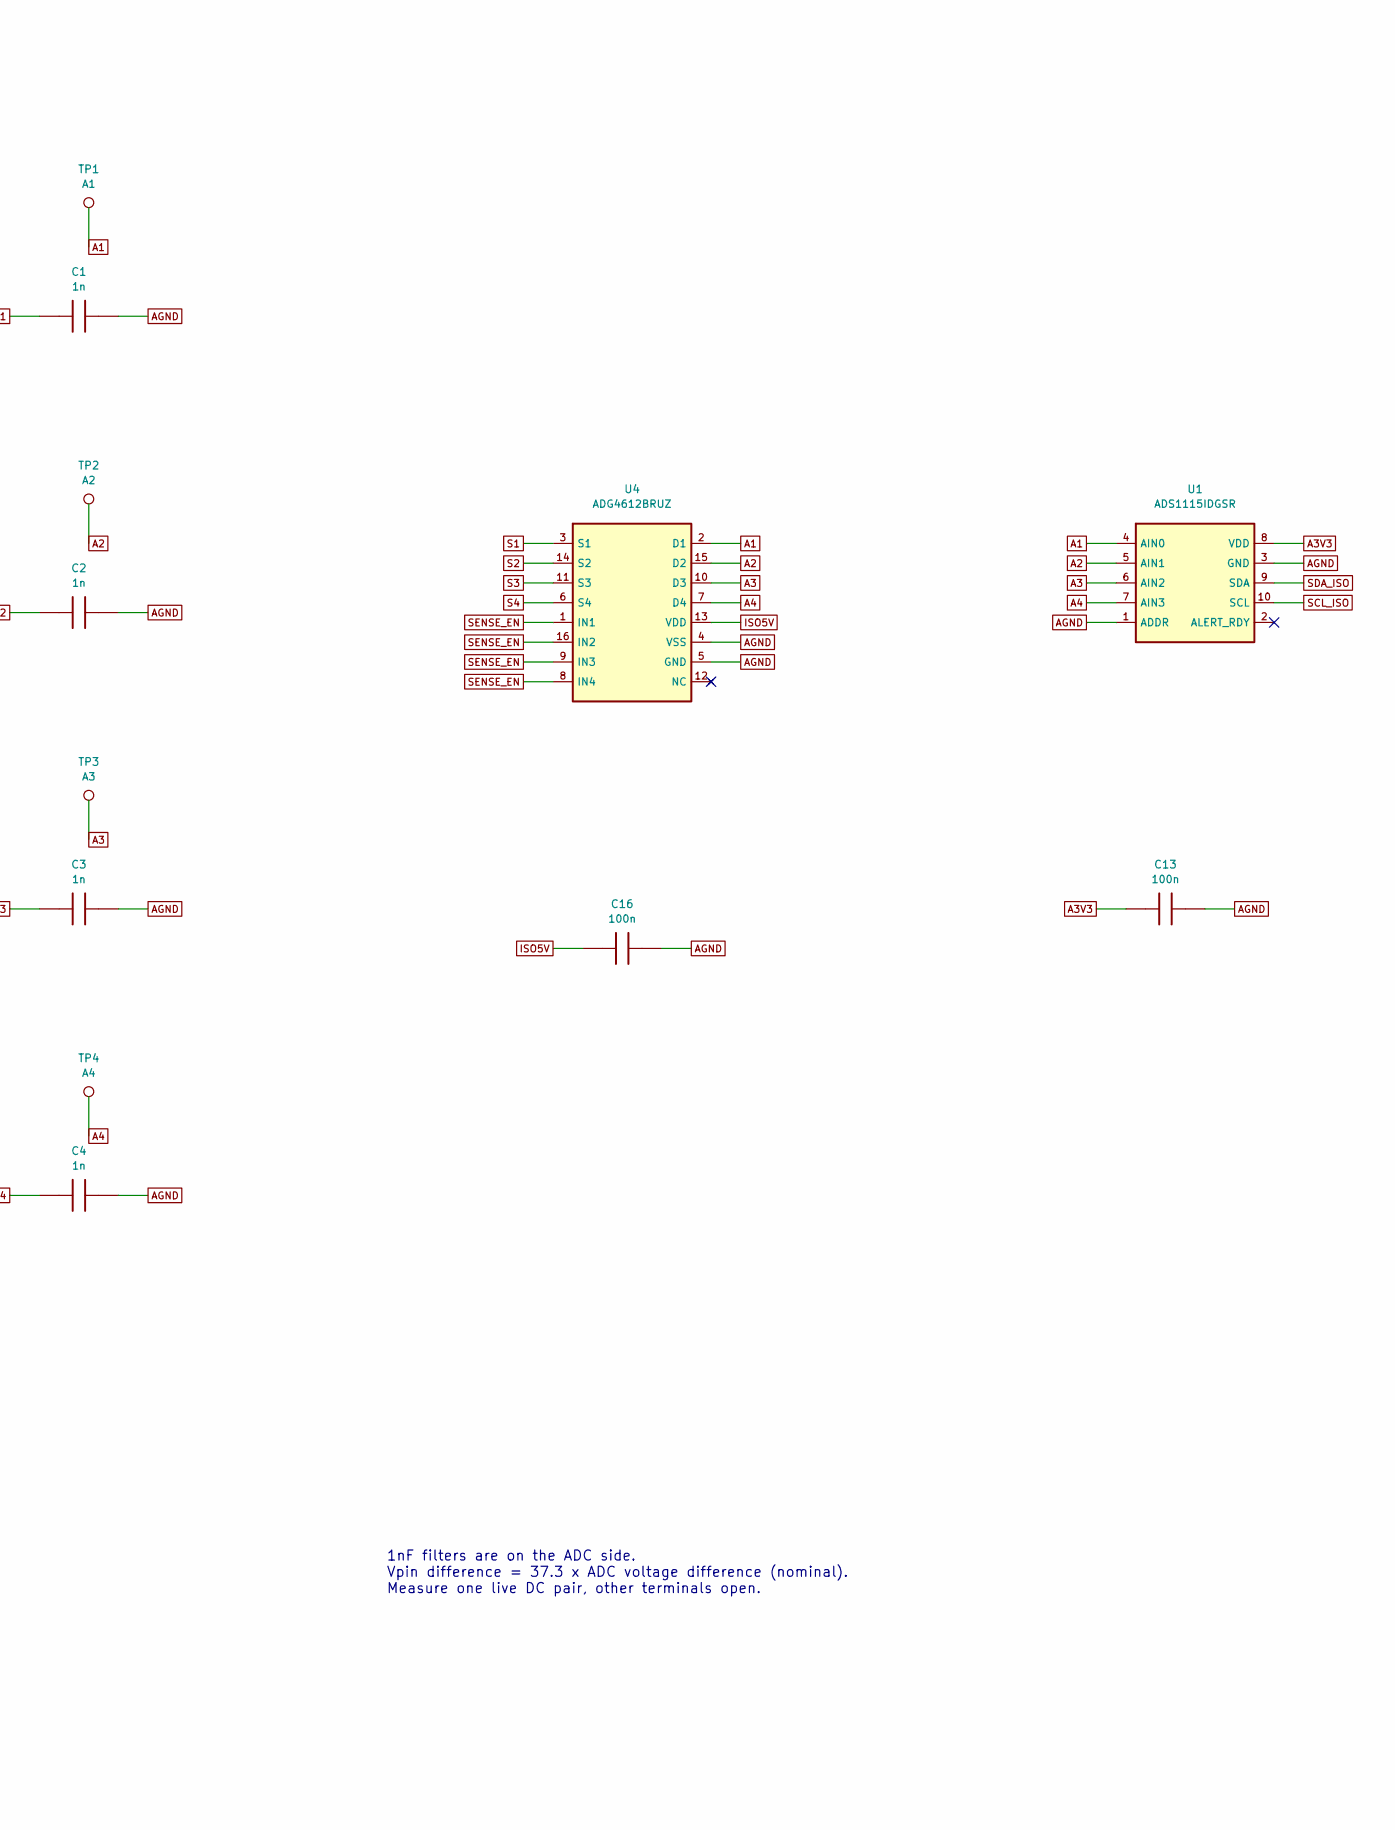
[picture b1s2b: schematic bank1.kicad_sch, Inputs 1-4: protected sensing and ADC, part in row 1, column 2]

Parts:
C1, C2, C3, C4: 1n; C_0805_2012Metric; MPN CC0805JRNPO9BN102; LCSC C62774
C13, C16: 100n; C_0805_2012Metric; MPN CC0805KRX7R9BB104; LCSC C49678
D1, D2, D3, D4: 12V clamp; D_SOD-123F; MPN BZT52H-C12,115; LCSC C282531
J1: INPUTS 1-4; TerminalBlock_Phoenix_PT-1,5-4-3.5-H_1x04_P3.50mm_Horizontal; MPN 1984633; LCSC C5144867
R1, R2, R4, R5, R7, R8, R10, R11: 165k; R_0805_2012Metric; MPN RT0805BRD07165KL; LCSC C865215
R3, R6, R9, R12: 10k; R_0805_2012Metric; MPN RT0805BRD0710KL; LCSC C110775
R46, R47, R48, R49: 100k; R_0805_2012Metric; MPN RT0805BRD07100KL; LCSC C122537
TP1: A1; TestPoint_Pad_D1.5mm
TP2: A2; TestPoint_Pad_D1.5mm
TP3: A3; TestPoint_Pad_D1.5mm
TP4: A4; TestPoint_Pad_D1.5mm
U1: ADS1115IDGSR; TSSOP-10_3x3mm_P0.5mm; MPN ADS1115IDGSR; LCSC C37593
U4: ADG4612BRUZ; TSSOP-16_4.4x5mm_P0.65mm; MPN ADG4612BRUZ-REEL7; LCSC C207399

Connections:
A1: C1.1, R3.1, TP1.1, U1.4 (AIN0), U4.2 (D1)
A2: C2.1, R6.1, TP2.1, U1.5 (AIN1), U4.15 (D2)
A3: C3.1, R9.1, TP3.1, U1.6 (AIN2), U4.10 (D3)
A3V3: C13.1, U1.8 (VDD); also elsewhere on the board
A4: C4.1, R12.1, TP4.1, U1.7 (AIN3), U4.7 (D4)
AGND: C1.2, C2.2, C3.2, C4.2, C13.2, C16.2, D1.2, D2.2, D3.2, D4.2, R46.2, R47.2, R48.2, R49.2, U1.1 (ADDR), U1.3 (GND), U4.4 (VSS), U4.5 (GND); also elsewhere on the board
ISO5V: C16.1, U4.13 (VDD); also elsewhere on the board
MID1: R1.2, R2.1
MID2: R4.2, R5.1
MID3: R7.2, R8.1
MID4: R10.2, R11.1
P1: J1.1, R1.1
P2: J1.2, R4.1
P3: J1.3, R7.1
P4: J1.4, R10.1
S1: D1.1, R2.2, R46.1, U4.3 (S1)
S2: D2.1, R5.2, R47.1, U4.14 (S2)
S3: D3.1, R8.2, R48.1, U4.11 (S3)
S4: D4.1, R11.2, R49.1, U4.6 (S4)
SCL_ISO: U1.10 (SCL); also elsewhere on the board
SDA_ISO: U1.9 (SDA); also elsewhere on the board
SENSE_EN: U4.1 (IN1), U4.8 (IN4), U4.9 (IN3), U4.16 (IN2); also elsewhere on the board
VBIAS: R3.2, R6.2, R9.2, R12.2; also elsewhere on the board

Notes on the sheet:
INPUTS 1-4: PROTECTED SENSING AND ADC
Two 165k resistors limit input current. D1-D12 clamp switch SOURCE pins only. 100k source bleeds permit startup with DUT connected. Switches isolate ADC and bias when disabled.
1nF filters are on the ADC side. Vpin difference = 37.3 x ADC voltage difference (nominal). Measure one live DC pair, other terminals open.
12V nominal; 0-18V intended measurement range. 48V DC miswire target requires prototype verification. Do not connect any terminal directly to AGND or USB_GND.
